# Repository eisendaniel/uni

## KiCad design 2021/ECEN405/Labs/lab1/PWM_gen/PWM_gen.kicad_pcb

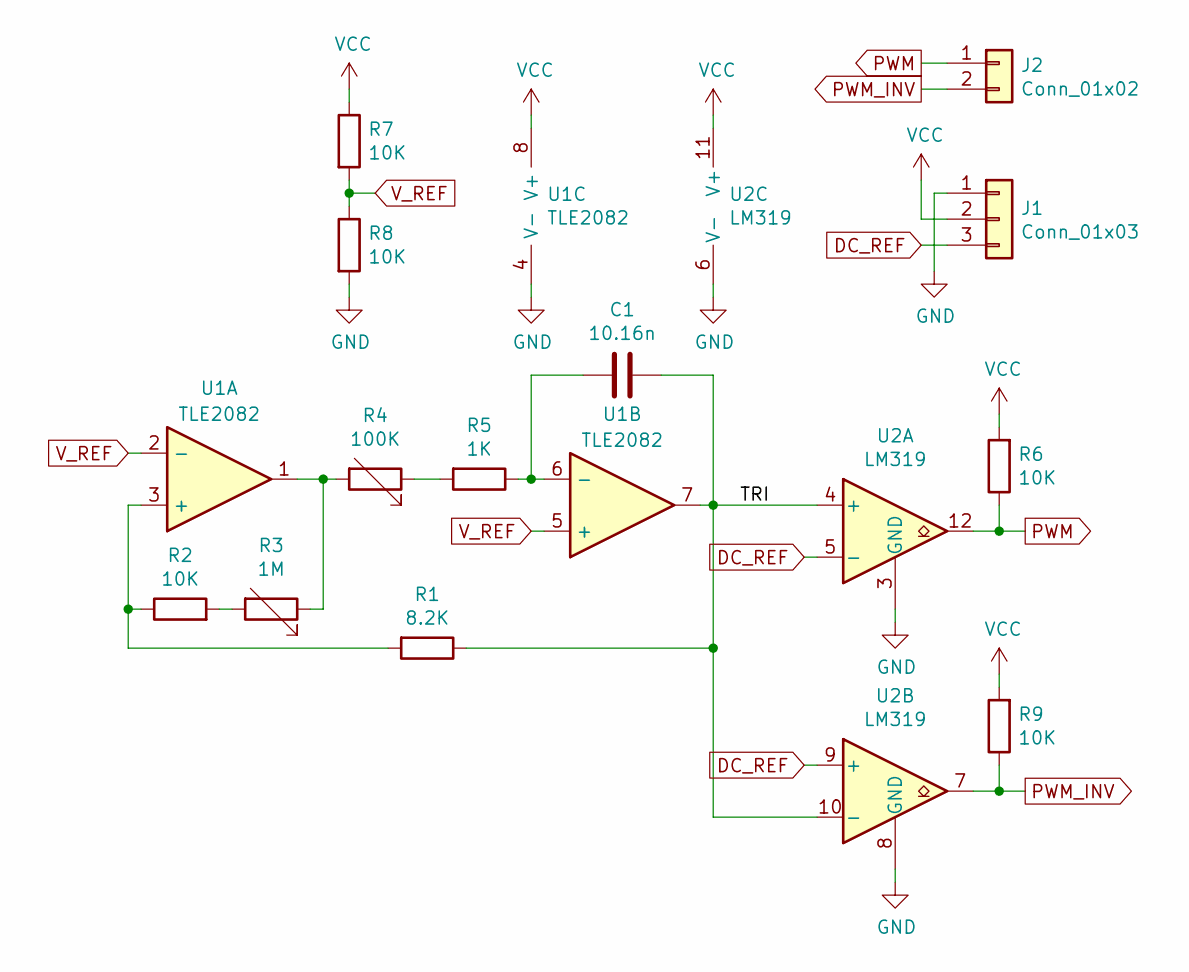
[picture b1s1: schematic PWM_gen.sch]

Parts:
C1: 10.16n; C_0805_2012Metric
J1: Conn_01x03; PinHeader_1x03_P2.54mm_Vertical
J2: Conn_01x02; PinHeader_1x02_P2.54mm_Vertical
R1: 8.2K; R_0805_2012Metric
R2, R6, R7, R8, R9: 10K; R_0805_2012Metric
R3: 1M; R_0805_2012Metric
R4: 100K; R_0805_2012Metric
R5: 1K; R_0805_2012Metric
U1: TLE2082; DIP-8_W7.62mm
U2: LM319; DIP-14_W7.62mm

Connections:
/TRI: C1.1, R1.1, U1.7, U2.4 (+), U2.10 (-)
DC_REF: J1.3, U2.5 (-), U2.9 (+)
GND: J1.1, R8.2, U1.4 (V-), U2.3 (GND), U2.6 (V-), U2.8 (GND)
unnamed: C1.2, R5.1, U1.6 (-)
unnamed: R1.2, R2.1, U1.3 (+)
unnamed: R2.2, R3.2
unnamed: R3.1, R4.2, U1.1
unnamed: R4.1, R5.2
PWM: J2.1, R6.1, U2.12
PWM_INV: J2.2, R9.1, U2.7
VCC: J1.2, R6.2, R7.1, R9.2, U1.8 (V+), U2.11 (V+)
V_REF: R7.2, R8.1, U1.2 (-), U1.5 (+)

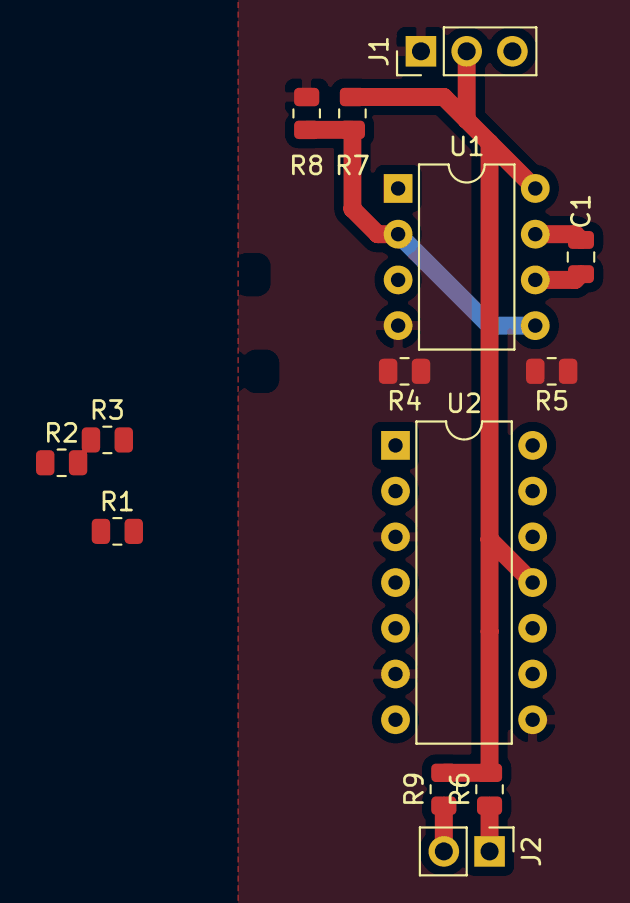
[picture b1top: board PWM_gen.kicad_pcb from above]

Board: 2 copper layers, 14 parts (0 on the bottom side), 12 nets.

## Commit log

2020-03-19 init
2020-03-19 textbook
2020-03-19 lab1
2020-03-19 lab2
2020-03-20 matlab stuff
2020-03-20 txtbooks
2020-03-20 add *
2020-03-20 update ignore
2020-03-21 update ignored
2020-03-21 week3 work
2020-03-21 engr201
2020-03-21 rm 2019
2020-03-22 lab pies
2020-03-23 ass 3 ecen321 tex
2020-03-23 add dictionary
2020-03-23 compiled pdf
2020-04-01 thursday
2020-04-06 lab work
2020-04-16 ecen303 ass 1
2020-04-16 directorty reorganising
2020-04-18 303 ass1
2020-04-25 303 material
2020-04-25 303 Assignment q3,5
2020-04-25 303 assigment 1, q6
2020-04-27 303 ass1 finished
2020-04-27 ecen321 ass3 q1 done
2020-05-03 week4 over
2020-05-03 week 4 301
2020-05-06 nwenass_1 tutoring files
2020-05-06 321 + 315
2020-05-11 321 lab2
2020-05-11 321 ass4,5
2020-05-12 321 ass5 finished
2020-05-12 added ass2 303
2020-05-13 303 ass2 q2 finished
2020-05-14 tex template and 315 ass2 init
2020-05-15 315ass2 complete
2020-05-20 week7 assignments
2020-05-23 week 7
2020-05-23 updt igne
2020-05-23 marking finished
2020-05-24 added 2019
2020-05-25 321 lab3 done
2020-06-08 week 10/11
2020-06-08 week 10-11
2020-06-15 week 10
2020-06-16 315 ass4 and 321 ass10
2020-06-25 315 final
2020-07-26 tri2_week2
2020-08-05 ecen301 and rese412
2020-08-10 wk4 labs
2020-08-14 ECEN301 lab 2 report complete
2020-08-16 ecen302 lab2
2020-08-18 rese report checkpoint
2020-08-19 RESE Proj 1 done
2020-08-31 second half begin
2020-09-03 ecen 301 lab 3
2020-09-04 ecen302 report and ass1
2020-09-06 302 ass1 complete
2020-09-07 rm summer
2020-09-07 rese_wh_updated
2020-09-08 rese migrate to desktop
2020-09-08 reser p2 almost done
2020-09-09 controller finished
2020-09-10 301_lab4_complete
2020-09-11 lab4_FSM complete
2020-09-13 week2_compl
2020-09-15 reshuffle 302
2020-09-20 start week 9?
2020-09-21 update: ignore
2020-09-22 rese p3 setup
2020-09-22 team-repo
2020-09-22 302 lab5
2020-09-30 302/301
2020-10-01 nwen and ass
2020-10-04 late stuff
2020-10-05 still very late, fuck
2020-10-07 rese report and labs
2020-10-08 report
2020-10-08 rese report
2020-10-09 pc sync
2020-10-12 late assignments
2020-10-13 late ass cont
2020-10-13 ecen 302, ass3
2020-10-14 ass 3 301 fin
2020-10-14 page breaks
2020-10-15 late labs
2020-10-19 late labs 8
2020-10-27 2020 complete
2020-11-09 1st day
2021-02-25 2021 init
2021-02-25 222 wk1
2021-02-25 222 1a-d
2021-02-27 222 ass1 compl. bar 4e
2021-02-27 export 222ass1
2021-02-27 headers/footers
2021-02-28 template 222
2021-02-28 ammended min/max
2021-02-28 clean up
2021-03-01 222 lab 1
2021-03-01 lab 222 1
2021-03-01 last q4
2021-03-02 222 ass 1 compl
2021-03-03 425 l6
2021-03-10 222 python fix
2021-03-11 wk3 compl
2021-03-13 ass1 425 compl
2021-03-14 ass2 start
2021-03-15 ass 2 cont
2021-03-15 rebuild
2021-03-15 ignore
2021-03-16 ass 2 1 done
2021-03-22 py 2morr
2021-03-23 compl
2021-03-28 2/3 done
2021-03-29 all but d
2021-03-29 all but DEEZ
2021-03-30 rebuild ignore
2021-03-31 solved k(y), oops
2021-04-25 tex stuff
2021-04-26 401 COE a1 0.5
2021-04-28 401 'compl'
2021-04-30 maff
2021-05-03 222 and 425 mech compl
2021-05-10 fin a3
2021-05-26 slides
2021-05-26 compress
2021-05-27 222ass5
2021-06-03 222 a6 n-1
2021-06-04 ass cont
2021-06-09 ass 6 compl
2021-06-17 222test coml
2021-07-13 lab 405
2021-07-18 lab1 done
2021-07-18 lit rev 426
2021-07-20 matlab yay
2021-07-26 4*5 ass
2021-07-26 fin l2
2021-07-27 fin no write
2021-07-31 ass1
2021-08-01 all but 1
2021-08-01 oops wrong name
2021-08-09 fin l4
2021-08-26 415 ass
2021-09-16 tri start
2021-09-21 pick n damp
2021-09-21 lab6
2021-09-22 lab 6
2021-09-23 lab 6 fin
2021-10-13 ass2 402
2021-10-16 ass is bad
2021-10-16 all but 9
2021-10-17 9 start
2021-10-17 format
2021-10-17 9 fin
2021-10-17 just do price
2021-10-17 fixed
2021-10-31 final
2021-11-04 filter sim
2021-11-06 dc r
2021-11-07 almost there
2021-11-07 fuck
2021-11-08 beans
